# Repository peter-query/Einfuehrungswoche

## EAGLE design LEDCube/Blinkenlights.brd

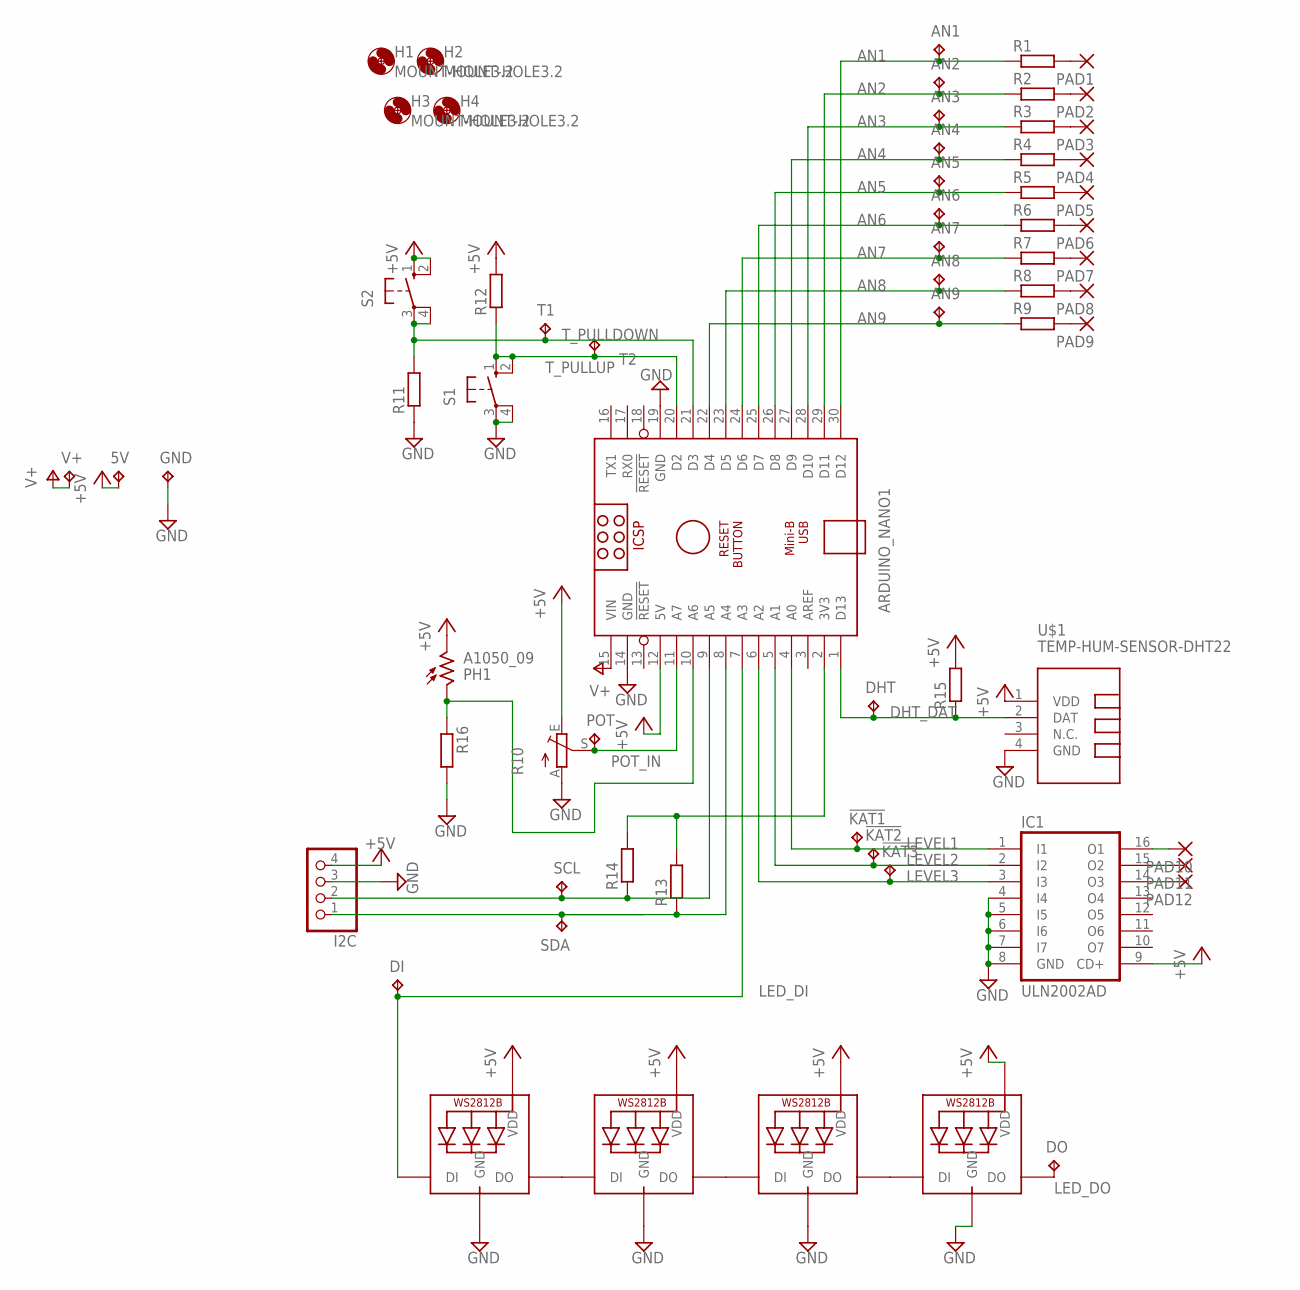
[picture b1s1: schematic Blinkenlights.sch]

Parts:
5V: TPPAD1-17; P1-17
!KAT1, !KAT2, !KAT3: TPB1,27; B1,27
AN1, AN2, AN3, AN4, AN5, AN6, AN7, AN8, AN9: TPB1,27; B1,27
ARDUINO_NANO1: ARDUINO_NANO
DHT: TPB1,27; B1,27
DI: TPB1,27; B1,27
DO: TPB1,27; B1,27
GND: TPPAD1-17; P1-17
H1, H2, H3, H4: MOUNT-HOLE3.2; 3,2
I2C: PINHD-1X4; 1X04
IC1: ULN2002AD; SO16
LED1, LED2, LED3, LED4: WS2812B5050; WS2812B
PAD1, PAD2, PAD3, PAD4, PAD5, PAD6, PAD7, PAD8, PAD9, PAD10, PAD11, PAD12: 2,54/1,1
PH1: A1050_09; T0-46-A10XX
POT: TPB1,27; B1,27
R1, R2, R3, R4, R5, R6, R7, R8, R9: R-EU_R0603; R0603
R10: TRIM_EU-RJ9W; RJ9W
R11, R12, R13, R14, R15, R16: R-EU_R0805; R0805
S1, S2: 10-XX; B3F-10XX
SCL: TPB1,27; B1,27
SDA: TPB1,27; B1,27
T1, T2: TPB1,27; B1,27
U$1: TEMP-HUM-SENSOR-DHT22
V+: TPPAD1-17; P1-17

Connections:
+5V: 5V.TP, ARDUINO_NANO1.12 (5V), I2C.4, IC1.9 (CD+), LED1.1-VDD (VDD), LED2.1-VDD (VDD), LED3.1-VDD (VDD), LED4.1-VDD (VDD), PH1.2, R10.E, R12.2, R15.2, S2.1 (S), S2.2 (S1), U$1.1 (VDD)
AN1: AN1.TP, ARDUINO_NANO1.30 (D12), R1.1
AN2: AN2.TP, ARDUINO_NANO1.29 (D11), R2.1
AN3: AN3.TP, ARDUINO_NANO1.28 (D10), R3.1
AN4: AN4.TP, ARDUINO_NANO1.27 (D9), R4.1
AN5: AN5.TP, ARDUINO_NANO1.26 (D8), R5.1
AN6: AN6.TP, ARDUINO_NANO1.25 (D7), R6.1
AN7: AN7.TP, ARDUINO_NANO1.24 (D6), R7.1
AN8: AN8.TP, ARDUINO_NANO1.23 (D5), R8.1
AN9: AN9.TP, ARDUINO_NANO1.22 (D4), R9.1
DHT_DAT: ARDUINO_NANO1.1 (D13), DHT.TP, R15.1, U$1.2 (DAT)
GND: ARDUINO_NANO1.14 (GND), ARDUINO_NANO1.19 (GND), GND.TP, I2C.3, IC1.4 (I4), IC1.5 (I5), IC1.6 (I6), IC1.7 (I7), IC1.8 (GND), LED1.3-GND (GND), LED2.3-GND (GND), LED3.3-GND (GND), LED4.3-GND (GND), R10.A, R11.1, R16.2, S1.3, S1.4 (P1), U$1.4 (GND)
LED_DI: ARDUINO_NANO1.7 (A3), DI.TP, LED1.4-DIN (DI)
LED_DO: DO.TP, LED4.2-DOUT (DO)
LEVEL1: !KAT1.TP, ARDUINO_NANO1.4 (A0), IC1.1 (I1)
LEVEL2: !KAT2.TP, ARDUINO_NANO1.5 (A1), IC1.2 (I2)
LEVEL3: !KAT3.TP, ARDUINO_NANO1.6 (A2), IC1.3 (I3)
unnamed: PAD1.1, R1.2
unnamed: PAD2.1, R2.2
unnamed: PAD3.1, R3.2
unnamed: PAD4.1, R4.2
unnamed: PAD5.1, R5.2
unnamed: PAD6.1, R6.2
unnamed: PAD7.1, R7.2
unnamed: PAD8.1, R8.2
unnamed: PAD9.1, R9.2
unnamed: IC1.16 (O1), PAD10.1
unnamed: IC1.15 (O2), PAD11.1
unnamed: IC1.14 (O3), PAD12.1
unnamed: LED1.2-DOUT (DO), LED2.4-DIN (DI)
unnamed: LED2.2-DOUT (DO), LED3.4-DIN (DI)
unnamed: ARDUINO_NANO1.2 (3V3), R13.2, R14.2
unnamed: LED3.2-DOUT (DO), LED4.4-DIN (DI)
unnamed: ARDUINO_NANO1.10 (A6), PH1.1, R16.1
unnamed: ARDUINO_NANO1.8 (A4), I2C.1, R13.1, SDA.TP
unnamed: ARDUINO_NANO1.9 (A5), I2C.2, R14.1, SCL.TP
POT_IN: ARDUINO_NANO1.11 (A7), POT.TP, R10.S
T_PULLDOWN: ARDUINO_NANO1.21 (D3), R11.2, S2.3, S2.4 (P1), T1.TP
T_PULLUP: ARDUINO_NANO1.20 (D2), R12.1, S1.1 (S), S1.2 (S1), T2.TP
V+: ARDUINO_NANO1.15 (VIN), V+.TP

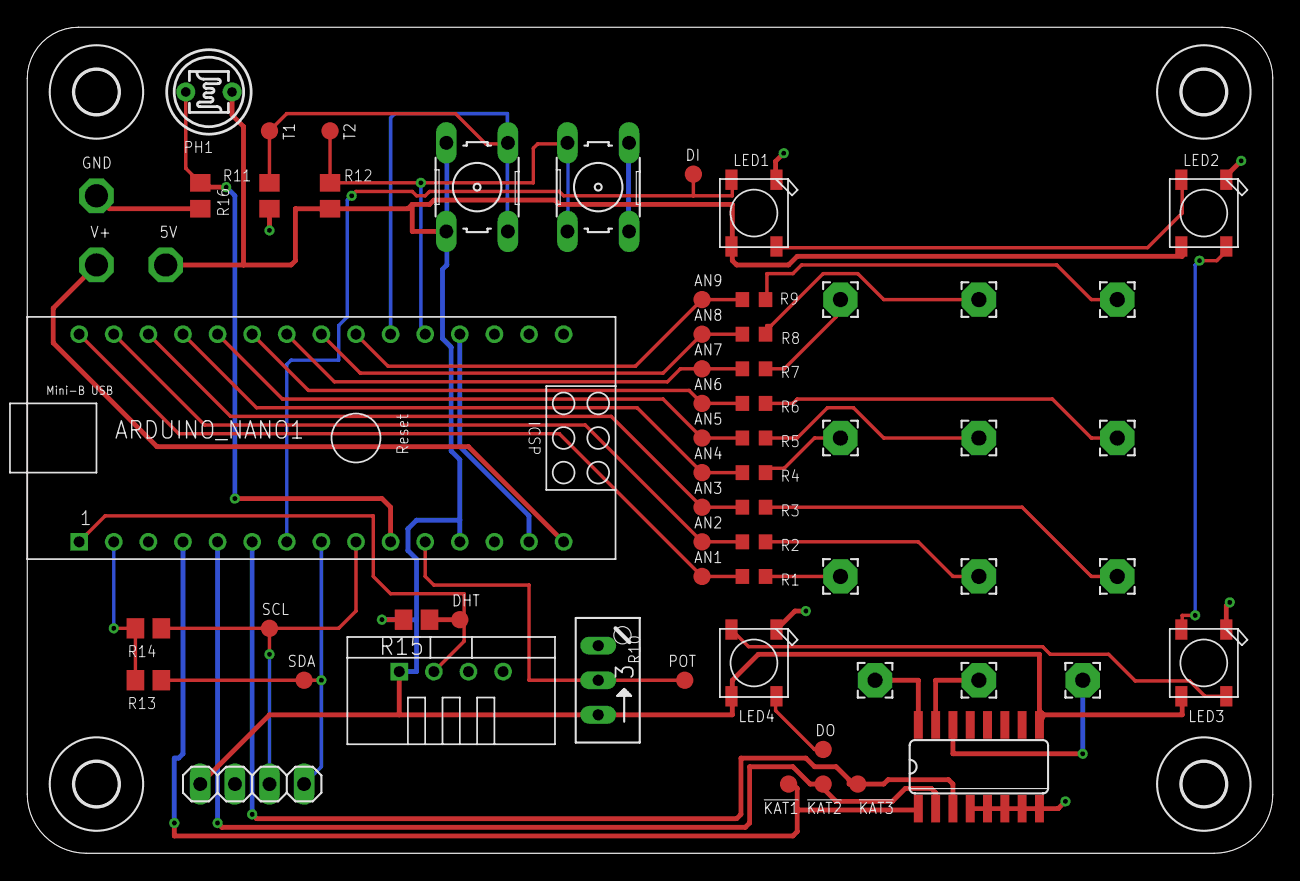
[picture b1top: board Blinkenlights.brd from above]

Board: 2 copper layers, 91.4 x 60.6 mm, 66 parts (0 on the bottom side), 40 nets.

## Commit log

2020-08-10 Init Latex file
2020-08-10 init game of life description
2020-08-11 wip game of life
2020-08-11 Aufgabe 1-3 hinzugefuegt, wegen latexproblemen mit neuem Dokument
2020-08-12 Aufabenstellung
2020-08-12 Aufgabestellung fertig
2020-08-12 added simple turtle example
2020-08-13 Add catch me
2020-08-13 Struktogramm Aufgaben hinzufgefügt
2020-08-14 strechhölzer
2020-08-18 added Aufgaben
2021-07-02 update commit

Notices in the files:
parts and their libraries:
diy-modules: Released under the Creative Commons Attribution 4.0 International License: http://creativecommons.org/licenses/by/4.0
